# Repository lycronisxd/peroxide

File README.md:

<h3 align="center">
<picture>
  <source media="(prefers-color-scheme: dark)" srcset="images/logo_white.png">
  <source media="(prefers-color-scheme: light)" srcset="images/logo_black.png">
  
</picture><br \>
<br \>
<picture>
  <source media="(prefers-color-scheme: dark)" srcset="images/name_white.png">
  <source media="(prefers-color-scheme: light)" srcset="images/name_black.png">
  
</picture><br \>
<br \>
a simple rp2040 dev board to teach me embedded electronics!
<br \>
<br \>
<div align="center">

</div>

</h3>
<hr>
<h2 align="center">about.</h2>

<h3 align="center">
pentoxide is a small intro for me into the world of embedded electronics,<br \>
since i find it extremely interesting and its extremely powerful<br \>
for making pcbs without breaking out a devboard!<br \>
<br \>
the rp2040 seemed like a good place to start,<br \>
since the routing philosophy is similar in some aspects<br \>
to the atmega32u4 (which i have experience with)<br \>
but was also able to learn routing for components like<br \>
flash memory and voltage regulators.<br \>
</h3>
<hr>

<h2 align="center">features.</h2><br \>
<h3 align="left">
<ul>
<li>rp2040 based</li>
<li>16 gpio pins</li>
<li>12 digital only pins</li>
<li>4 analog+digital pins</li>
<li>5v</li>
<li>3v3</li>
<li>usb-c</li>
</ul>
</h4>
<hr>

<h2 align="center">showcase.</h2>
<p align="center">
<br \>
<br \>
<br \>
<br \>
<br \>
<br \>
<br \>

</p>
<hr>
<h2 align="center">bill of materials.</h2><br \>

|part                                |type    |quantity|unit price (USD)|line total (USD)|link|vendor|funding|notes                                                   |
|------------------------------------|--------|--------|----------------|----------------|----|------|-------|--------------------------------------------------------|
|peroxide pcb                        |PCB     |5       |0.80            |4.00            |    |jlcpcb|Grant  |this is the cheapest option jlcpcb has                  |
|peroxide pcb assembly               |PCB     |2       |33.755          |67.51           |    |jlcpcb|Grant  |this is the lowest no. of assembled parts i could get :(|
|global standard direct line shipping|Shipping|1       |7.67            |7.67            |    |jlcpcb|Grant  |this is the cheapest option jlcpcb has                  |
|total                               |        |        |                |79.18           |    |      |       |                                                        |

<hr>
<h2 align="center">relevant links.</h2>
<h3>
link to repo pcb files<br \>
<a href="https://github.com/lycronisxd/peroxide/tree/main/pcb">lycronisxd/peroxide/pcb</a><br \>
<br \>
link to pcbway quote / component bill of materials<br \>
<a href="https://github.com/lycronisxd/peroxide/blob/main/peroxide_pcbway_quote_bom.xls">lycronisxd/peroxide/peroxide_pcbway_quote_bom.xls</a><br \>
<br \>
link to a-shift<br \>
<a href="https://github.com/lycronisxd/a-shift">lycronisxd/a-shift</a><br \>
<br \>
link to pentoxide<br \>
<a href="https://github.com/lycronisxd/pentoxide">lycronisxd/pentoxide</a><br \>
<br \>
link to e-split<br \>
<a href="https://github.com/lycronisxd/e-split">lycronisxd/e-split</a><br \>
<br \>
link to polylactic<br \>
<a href="https://github.com/lycronisxd/polylactic">lycronisxd/polylactic</a>
</h3>
<hr>

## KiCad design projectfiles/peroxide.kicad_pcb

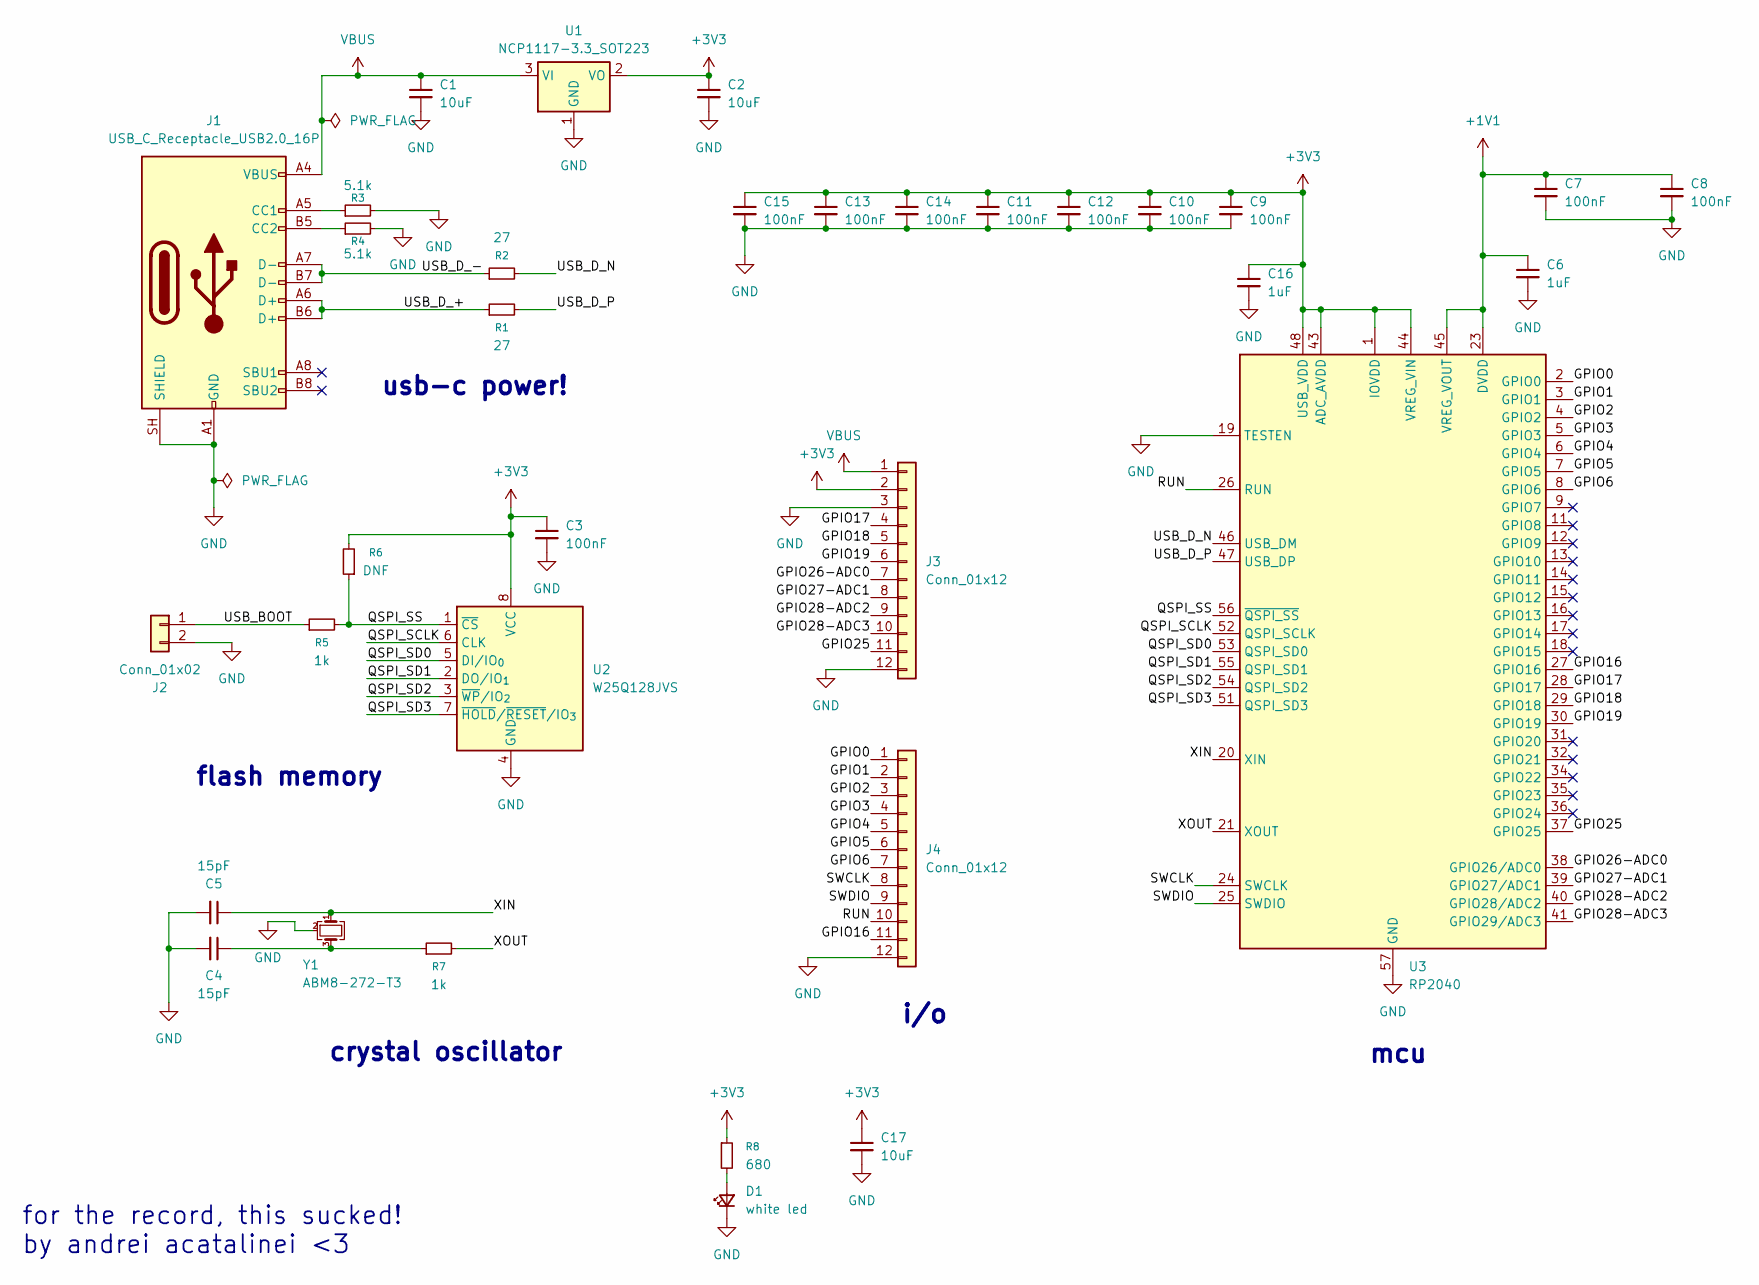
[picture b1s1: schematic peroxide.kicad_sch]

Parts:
C1, C2, C17: 10uF; C_0402_1005Metric
C3, C7, C8, C9, C10, C11, C12, C13, C14, C15: 100nF; C_0402_1005Metric
C4, C5: 15pF; C_0402_1005Metric
C6, C16: 1uF; C_0402_1005Metric
D1: white led; LED_0603_1608Metric
J1: USB_C_Receptacle_USB2.0_16P; USB_C_Receptacle_HRO_TYPE-C-31-M-12
J2: Conn_01x02; PinHeader_1x02_P2.54mm_Vertical
J3, J4: Conn_01x12; PinHeader_1x12_P2.54mm_Vertical
R1, R2: 27; R_0402_1005Metric
R3, R4: 5.1k; R_0402_1005Metric
R5, R7: 1k; R_0402_1005Metric
R6: DNF; R_0402_1005Metric
R8: 680; R_0402_1005Metric
U1: NCP1117-3.3_SOT223; SOT-223-3_TabPin2
U2: W25Q128JVS; SOIC-8_5.3x5.3mm_P1.27mm
U3: RP2040; QFN-56-1EP_7x7mm_P0.4mm_EP3.2x3.2mm
Y1: ABM8-272-T3; Crystal_SMD_3225-4Pin_3.2x2.5mm

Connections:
+1V1: C6.1, C7.1, C8.1, U3.23 (DVDD), U3.45 (VREG_VOUT), U3.50 (DVDD)
+3V3: C2.1, C3.1, C9.1, C10.1, C11.1, C12.1, C13.1, C14.1, C15.1, C16.1, C17.1, J3.2, R6.2, R8.1, U1.2 (VO), U2.8 (VCC), U3.1 (IOVDD), U3.10 (IOVDD), U3.22 (IOVDD), U3.33 (IOVDD), U3.42 (IOVDD), U3.43 (ADC_AVDD), U3.44 (VREG_VIN), U3.48 (USB_VDD), U3.49 (IOVDD)
/GPIO0: J4.1, U3.2 (GPIO0)
/GPIO1: J4.2, U3.3 (GPIO1)
/GPIO2: J4.3, U3.4 (GPIO2)
/GPIO3: J4.4, U3.5 (GPIO3)
/GPIO4: J4.5, U3.6 (GPIO4)
/GPIO5: J4.6, U3.7 (GPIO5)
/GPIO6: J4.7, U3.8 (GPIO6)
/GPIO16: J4.11, U3.27 (GPIO16)
/GPIO17: J3.4, U3.28 (GPIO17)
/GPIO18: J3.5, U3.29 (GPIO18)
/GPIO19: J3.6, U3.30 (GPIO19)
/GPIO25: J3.11, U3.37 (GPIO25)
/GPIO26-ADC0: J3.7, U3.38 (GPIO26/ADC0)
/GPIO27-ADC1: J3.8, U3.39 (GPIO27/ADC1)
/GPIO28-ADC2: J3.9, U3.40 (GPIO28/ADC2)
/GPIO28-ADC3: J3.10, U3.41 (GPIO29/ADC3)
/QSPI_SCLK: U2.6 (CLK), U3.52 (QSPI_SCLK)
/QSPI_SD0: U2.5 (DI/IO_{0}), U3.53 (QSPI_SD0)
/QSPI_SD1: U2.2 (DO/IO_{1}), U3.55 (QSPI_SD1)
/QSPI_SD2: U2.3 (~WP/IO_{2}), U3.54 (QSPI_SD2)
/QSPI_SD3: U2.7 (~HOLD/~RESET/IO_{3}), U3.51 (QSPI_SD3)
/QSPI_SS: R5.2, R6.1, U2.1 (~CS), U3.56 (~QSPI_SS)
/RUN: J4.10, U3.26 (RUN)
/SWCLK: J4.8, U3.24 (SWCLK)
/SWDIO: J4.9, U3.25 (SWDIO)
/USB_BOOT: J2.1, R5.1
/USB_D_+: J1.A6 (D+), J1.B6 (D+), R1.1
/USB_D_-: J1.A7 (D-), J1.B7 (D-), R2.1
/USB_D_N: R2.2, U3.46 (USB_DM)
/USB_D_P: R1.2, U3.47 (USB_DP)
/XIN: C5.1, U3.20 (XIN), Y1.1
/XOUT: R7.2, U3.21 (XOUT)
GND: C1.2, C2.2, C3.2, C4.2, C5.2, C6.2, C7.2, C8.2, C9.2, C10.2, C11.2, C12.2, C13.2, C14.2, C15.2, C16.2, C17.2, D1.1 (K), J1.A1 (GND), J1.A12 (GND), J1.B1 (GND), J1.B12 (GND), J1.SH (SHIELD), J2.2, J3.3, J3.12, J4.12, R3.2, R4.2, U1.1 (GND), U2.4 (GND), U3.19 (TESTEN), U3.57 (GND), Y1.2 (G), Y1.4 (G)
unnamed: C4.1, R7.1, Y1.3
unnamed: D1.2 (A), R8.2
unnamed: J1.A5 (CC1), R3.1
unnamed: J1.B5 (CC2), R4.1
VBUS: C1.1, J1.A4 (VBUS), J1.A9 (VBUS), J1.B4 (VBUS), J1.B9 (VBUS), J3.1, U1.3 (VI)

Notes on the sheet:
i/o
flash memory
mcu
for the record, this sucked! by andrei acatalinei <3
usb-c power!
crystal oscillator

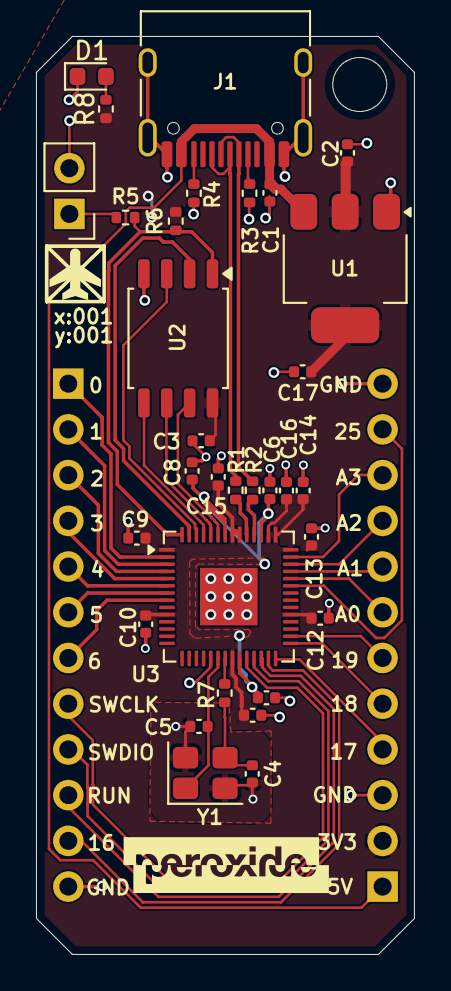
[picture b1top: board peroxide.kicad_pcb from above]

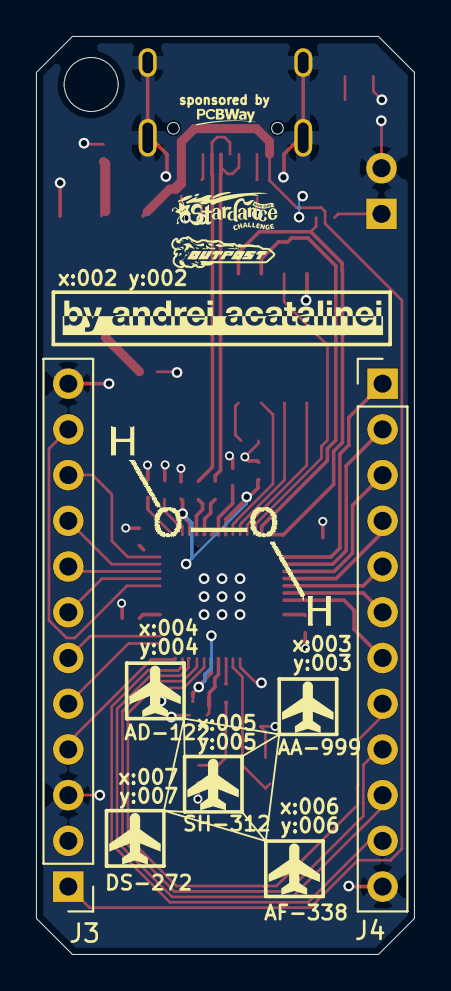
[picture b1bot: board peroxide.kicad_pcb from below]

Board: 2 copper layers, 21.0 x 51.0 mm, 34 parts (2 on the bottom side), 40 nets.
